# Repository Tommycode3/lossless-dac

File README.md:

# lossless-dac

A balanced headphone amplifier board: ±5 V rails from LT3045/LT3094 LDOs and one OPA1622 per channel, designed in [Zener](https://docs.pcb.new) to sit behind off-the-shelf Amanero (USB to I²S) and ES9038Q2M (DAC) modules. The custom board only does the two things that set what you hear at the jack, the analog rails and the output stage; the hard digital parts are bought as modules. Estimated amplifier noise is 1.4 µV RMS differential, which the DAC module will dominate.

Status: schematic captured as code (33 components, builds), layout not started. Nothing fabricated or measured; all performance figures are datasheet-derived.

| Parameter | Value |
|---|---|
| Input power | ±9 V dual rail, 3-pin header (+9 / GND / −9) |
| Analog rails | +4.99 V (LT3045EDD), −4.99 V (LT3094EDD), R_SET = 49.9 kΩ |
| LDO output noise | 0.8 µV RMS (10 Hz–100 kHz), each rail |
| LDO PSRR at 1 MHz | 76 dB (LT3045), 74 dB (LT3094) |
| LDO current limit | 500 mA per rail (R_ILIM_P = 300 Ω, R_ILIM_N = 7.5 kΩ) |
| Power-good (+ rail) | ≈ 4.92 V (93.1 k / 6.04 k on PGFB) |
| Amplifier | 2× OPA1622IDRCR (VSON-10), unity buffer (+) and unity inverter (−) per channel |
| Gain | +6.02 dB differential (×2), 0 dB single-ended (×1) |
| Input coupling | 2.2 µF / 100 kΩ, f₋₃dB ≈ 0.72 Hz |
| Outputs | balanced 5-pin (L+ R+ L− R− GND) for 4.4 mm; TRS (L, R, GND) for 6.35 mm |
| PCB | 4 copper layers |

There is no switching regulator on the board, so the ±9 V must come from a clean external supply. The modules are not on this board either, only the header for the DAC's single-ended L/R output. Connectors for the DAC, power input and both jacks are 2.54 mm pin headers standing in for the real parts.

## Building

Requires the Zener `pcb` toolchain (builds with `pcb` 0.4.6 and 0.4.95; `pcb.toml` pins `pcb-version = "0.4"`). Note that `pcb` may update itself when invoked.

```sh
pcb build lossless-dac.zen    # expect "✓ lossless-dac.zen (33 components)"
pcb layout lossless-dac.zen   # syncs the netlist into layout/layout.kicad_pcb and opens KiCad (--no-open to skip)
```

The Zener standard library and KiCad footprint libraries (~36 MB) are not committed. `pcb build` materialises them into `.pcb/stdlib/` on first run, and `layout/fp-lib-table` points there. Generated files (`layout/default.net`, `layout/snapshot.layout.json`, `layout/*.log`, `layout/.history/`) are ignored.

`pcb build` 0.4.95 currently warns about ten power pins tied to plain `Net`s instead of `Power()`/`Ground()` nets. 0.4.6 also reported no house-part match for the 2.2 µF 0805 capacitor and the 3- and 5-pin headers.

The circuit is in `lossless-dac.zen`, per-part modules, symbols and footprints in `components/`, the KiCad board in `layout/`.

## Rails

The LT3045/LT3094 SET pin sources/sinks a precision 100 µA (±1 %), so $V_{OUT} = \pm 100\ \mu\text{A} \times 49.9\ \text{k}\Omega = \pm 4.99\ \text{V}$. The 4.7 µF on SET filters the reference, which is what gets the regulators down to 0.8 µV RMS. The current limits and power-good threshold:

$$
I_{LIM,+} = \frac{150\ \text{mA·k}\Omega}{0.3\ \text{k}\Omega} = 500\ \text{mA},
\qquad
I_{LIM,-} = \frac{3.75\ \text{A·k}\Omega}{7.5\ \text{k}\Omega} = 500\ \text{mA},
\qquad
V_{PG} = 0.3\ \text{V} \times \left(1 + \frac{93.1\ \text{k}}{6.04\ \text{k}}\right) \approx 4.92\ \text{V}
$$

Headroom is about 4 V, far above the ~260 mV dropout, and it costs dissipation. At idle (OPA1622 $I_Q$ = 2.6 mA per channel, four channels in two duals) each LDO burns $4\ \text{V} \times 4 \times 2.6\ \text{mA} \approx 42\ \text{mW}$. At the 500 mA limit it would be 2 W per DFN package. If heavy loads are expected, the next step is a lower input voltage or using the LT3094's VIOC pin (unused for now) to steer an upstream pre-regulator.

The OPA1622's supply rejection is 0.1 µV/V typical (−140 dB), so rail noise referred to the amplifier input is $0.8\ \mu\text{V} \times 10^{-7} \approx 8 \times 10^{-14}\ \text{V}$. For the op-amps alone these LDOs are overkill. They would start to matter if the DAC module's analog stage were powered from the same rails, and that is the better argument for keeping them.

## Output stage

Unit A is a follower and unit B an inverter with $R_F = R_G = 1\ \text{k}\Omega$ fed from unit A, so $V_{L+} = V_{in}$, $V_{L-} = -V_{in}$ and $V_{\text{diff}} = 2V_{in}$ (+6.02 dB). The single-ended jack takes $V_{L+}$ directly. The input high-pass is $1/(2\pi \cdot 100\ \text{k}\Omega \cdot 2.2\ \mu\text{F}) \approx 0.72\ \text{Hz}$, ignoring the module's output impedance.

For noise, take $e_n = 2.8\ \text{nV}/\sqrt{\text{Hz}}$ at 1 kHz and 4.07 nV/√Hz for a 1 kΩ resistor at 300 K. Unit A's noise appears at both L+ and L−, so it doubles in the differential output; unit B runs at a noise gain of 2; each resistor reaches the output with gain 1:

$$
e_{o,\text{diff}} = \sqrt{(2 e_{n,A})^2 + (2 e_{n,B})^2 + e_{R_F}^2 + e_{R_G}^2}
= \sqrt{5.6^2 + 5.6^2 + 4.07^2 + 4.07^2} \approx 9.8\ \text{nV}/\sqrt{\text{Hz}}
$$

Current noise (0.8 pA/√Hz into 1 kΩ, 0.8 nV/√Hz) is negligible, and so is the 100 kΩ bias resistor, which the 2.2 µF and a low-impedance source shunt above a few hertz (about 0.03 nV/√Hz at 1 kHz). Over 20 Hz–20 kHz that gives $9.8\ \text{nV}/\sqrt{\text{Hz}} \times \sqrt{20\ \text{kHz}} \approx 1.4\ \mu\text{V RMS}$.

At ±5 V the OPA1622 datasheet gives 95 mW into 16 Ω and 150 mW into 32 Ω single-ended, both current-limited, and 11.3 mW into 600 Ω, voltage-limited. Bridging doubles the voltage across the load but not the current through it, so the balanced output gives about 4× the power when voltage-limited and about the same when current-limited:

| Load | Single-ended (datasheet) | Balanced (estimate) |
|---|---:|---:|
| 32 Ω | 150 mW | ≈ 150 mW (current-limited) |
| 600 Ω | 11.3 mW | ≈ 45 mW (voltage-limited) |

Balanced drive buys headroom for high-impedance headphones; for 16–32 Ω it gives symmetric drive and no extra power. Datasheet THD+N single-ended at those maximum powers is −118.7 dB (32 Ω) and −119.4 dB (600 Ω), and −132 dB at 1 kHz, G = 1, 3.5 V RMS into 2 kΩ. Taking 45 mW into 600 Ω as full scale ($V_{FS} \approx 5.2\ \text{V RMS}$), the amplifier-only unweighted dynamic range is $20 \log_{10}(5.2\ \text{V} / 1.4\ \mu\text{V}) \approx 131\ \text{dB}$, an upper bound the DAC module will set in practice.

## Not done yet

- Real connectors (4.4 mm, 6.35 mm, DC input, module headers) not chosen.
- Layout: footprints auto-placed, no outline, no routing, no pours.
- No design review or simulation.
- No Gerber or BOM/CPL; the board cannot be ordered.
- No measurements.

## License

Hardware design files (Zener sources, symbols, footprints, KiCad layout) and documentation: CERN-OHL-S-2.0 ([`LICENSE`](LICENSE)).

The LT3045/LT3094/OPA1622 footprints and symbols in `components/` are adapted from the KiCad libraries (CC-BY-SA 4.0 with the KiCad libraries exception) and remain under that licence. Datasheets are the property of Analog Devices and Texas Instruments and are not redistributed here.

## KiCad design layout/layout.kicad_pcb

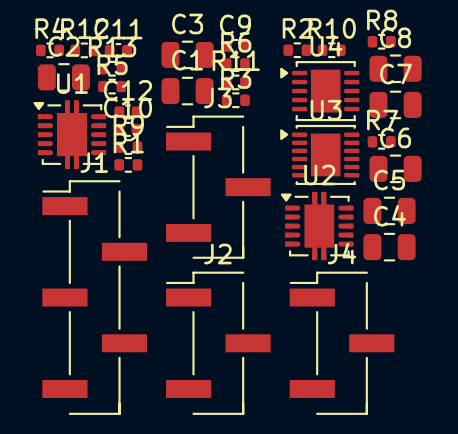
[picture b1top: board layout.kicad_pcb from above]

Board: 4 copper layers, 33 parts (0 on the bottom side), 21 nets, no tracks yet.

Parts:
C1, C2: 2.2uF; C_0805_2012Metric
C3, C4, C5, C6: GRM21BZ71E106KE15K; C_0805_2012Metric
C7, C8: GRM21BZ71H475KE15K; C_0805_2012Metric
C9, C10, C11, C12: GCM155R71H104KE02D; C_0402_1005Metric
J1: 2.54mm 5 x 1 SMD Vertical Male; PinHeader_1x05_P2.54mm_Vertical_SMD_Pin1Left
J2, J3, J4: 2.54mm 3 x 1 SMD Vertical Male; PinHeader_1x03_P2.54mm_Vertical_SMD_Pin1Left
R1, R2, R11: ERJ-2RKF1003X; R_0402_1005Metric
R3, R4, R5, R6: ERJ-2RKF1001X; R_0402_1005Metric
R7: ERJ-2RKF7501X; R_0402_1005Metric
R8: ERJ-2RKF3000X; R_0402_1005Metric
R9: ERJ-2RKF9312X; R_0402_1005Metric
R10: ERJ-2RKF6041X; R_0402_1005Metric
R12, R13: ERJ-2RKF4992X; R_0402_1005Metric
U1, U2: OPA1622IDRCR; OPA1622
U3: LT3094EDD#PBF; LT3094
U4: LT3045EDD#PBF; LT3045

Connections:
DAC_L: C1.1, J2.1
DAC_R: C2.1, J2.3
GND: C3.2, C4.2, C5.2, C6.2, C7.2, C8.2, C9.2, C10.2, C11.2, C12.2, J1.5, J2.2, J3.2, J4.3, R1.2, R2.2, R7.2, R8.2, R10.2, R12.2, R13.2, U1.3, U1.5, U2.3, U2.5, U3.9, U4.8, U4.11
ILIM_N: R7.1, U3.6
ILIM_P: R8.1, U4.5
L_INBUF: C1.2, R1.1, U1.1
L_INV: R3.2, R5.2, U1.6
L_NEG: J1.3, R3.1, U1.7
L_POS: J1.1, J4.1, R5.1, U1.9, U1.10
PGFB_P: R9.2, R10.1, U4.6
PG_POS: R11.1, U4.4
R_INBUF: C2.2, R2.1, U2.1
R_INV: R4.2, R6.2, U2.6
R_NEG: J1.4, R4.1, U2.7
R_POS: J1.2, J4.2, R6.1, U2.9, U2.10
SET_N: C7.1, R12.1, U3.8
SET_P: C8.1, R13.1, U4.7
VA_NEG: C5.1, C9.1, C10.1, U1.4, U1.11, U2.4, U2.11, U3.5, U3.10, U3.11, U3.12
VA_POS: C6.1, C11.1, C12.1, R9.1, R11.2, U1.2, U1.8, U2.2, U2.8, U4.9, U4.10
VIN_N: C3.1, J3.3, U3.1, U3.2, U3.3, U3.13
VIN_P: C4.1, J3.1, U4.1, U4.2, U4.3
